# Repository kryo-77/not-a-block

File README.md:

# Not-a-block
Note block from Minecraft but in real life.

## What it is:
I made a note block from Minecraft which functions close enough to the actual game. You can tap the top face of the note block to play it and hit the back side of it to change the pitch (like right-clicking in Minecraft).

You can change the sound of the note block by placing it on different types of blocks as well. This is possible as there is an RFID card reader underneath the note block and a RFID tag on top of the instrument block (like stone, glass, sand, etc.)

## How it works:
The note block contains an ESP-32-C3-SuperMini. It's the microcontroller which connects to different components. It also stores music files inside its flash memory. 
As the music files are under a second, we can store quite a lot of them inside the ESP32, so there is no need for a SD card module (which also saves pins). Sound is played by a MAX98357A I2S amp with a 4Ω 3W speaker (50mm diameter).

There are 2 piezoelectric sensors present inside the note block's top and back surface. When you hit the surface, the piezo sends voltage to the ESP32's data pin which tells it to play the sound.

There are 16 different instrument sounds which the note block can play, which depend on the block below it. When the top surface is hit, it only tells ESP32 to play a single sound each time. When the back surface is hit, which is for changing the pitch of the instrument, each hit changes the sound to a different pitch. We don't need to have different audio inside the ESP32 for each pitch, as it can directly change on its own. Only the instrument sounds are needed to be stored.

For detecting which block is present below the note block, a PN532 RFID card reader sits on the bottom surface, while a RFID tag sits on the top surface of the other blocks. 
The tag gets read every few seconds so that if the block changes, its sound changes as well without a lot of delay. 4 magnets are also present under the note block's surface as well as an instrument block's top surface, so that lining up the tags as well as the blocks is very easy. The magnets are also in different polarities (NN/SS) on the surfaces so you don't accidentally misplace back of the note block (where you hit to change pitch).

The front surface of the note block contains holes so that the speaker can output sound. I decided to only make holes in the black layer as it is thinner than the white one and would not show that many holes as well. 

## Dimensions:
1) Note block / Instrument block: 10 x 10 x 10 cm
  - Each face has 3 layers, overall 0.4cm thick.
2) Note block PCB: 5.75 x 4 cm
3) Piezoelectric sensor: 3.5cm diameter

## Files:
- `CAD` folder contains .f3d (fusion) file & .stl for printing.
- `PCB` folder contains kicad files, `export.zip` has gerber files, `3d_model` has .step file of PCB. It has a `footprints_ext` folder which contains footprint for ESP32-C3-SuperMini which I downloaded online.
- `CODE` folder contains basic test code (when RFID card gets detected, a beep is produced) which uses a XIAO s3, MFRC522 RFID reader and no piezo sensor. I only had these components with me so code are based on it instead of the BOM.

## How to assemble / Details about the 3d printed parts (!!WIP!!)

There are two types of block: Note block and Instrument block. Note block contains the electronics while the instrument block only contains a single RFID tag + 4 magnets on its top surface.

There are 6 parts per block. Final assembly should measure 10x10x10cm.

The faces are different sizes as all need to fit together to form the 10x10x10cm. It is pretty easy to assemble as same dimension face are opposites of each other. 

Each face has a rectangular hole on its bottom surface and a rectangle sticking out on its top surface. 
The hole attaches to the `base plate`, while the rectangle goes in the `top plate`

Thats it for the assembly, just pushing the faces on to the base, no need for screws. Though the design might get changed depending on it actually works irl as I cant test the prints myself.

Screws aren't really needed other than mounting the pcb, that too is optional as I've made standoffs on the base plate. 

## PCB schematic / render

## BOM
| No | Component | Qty | Unit Price (USD) | Uses | Link |
|----|-----------|-----|------------------|------|------|
| 1 | ESP32-C3 SuperMini | 1 | 2.72 | MCU | https://makerbazar.in/products/esp32-c3-supermini-iot-development-board |
| 2 | PN532 RFID/NFC V3 module | 1 | 2.83 | RFID reader | https://robocraze.com/products/nfc-near-field-communication-rf-id-v3-module |
| 3 | MAX98357A I2S amplifier | 1 | 2.04 | Sound amplifier | https://robu.in/product/smartelex-i2s-audio-breakout-max98357a/ |
| 4 | Speaker, 4 ohm 3W | 1 | 1.05 | Sound output | Local shop |
| 5 | 35mm piezo sensor | 2 | 0.23 | Hit and pitch sensing | https://robocraze.com/products/35mm-piezo-sensor |
| 6 | BZX55C3V3 zener diode | 2 | 0.02 | Piezo protection | https://robu.in/product/bzx55c3v3-1-2w-zener-diode-pack-of-40/ |
| 7 | 4.7k resistor | 2 | n/a | Piezo protection | |
| 8 | 470uF polarised capacitor | 1 | n/a | Power smoothing | |
| 9 | 1N5819 Schottky diode | 1 | 0.06 | Power protection (USB and battery connected together) | https://robu.in/product/1n5819-ap-mcc-40v-1a-600mv1a-do-41-schottky-diodes-rohs/ |
| 10 |	3d print |	1 |	14.55 |	3d print | (printing legion channel - slack)	https://print.speedhawks.online/slice |
| 11 |	PCB |	1 |	9.48 |	PCB manufacturing	| https://robu.in/product/online-pcb-manufacturing-service/ |

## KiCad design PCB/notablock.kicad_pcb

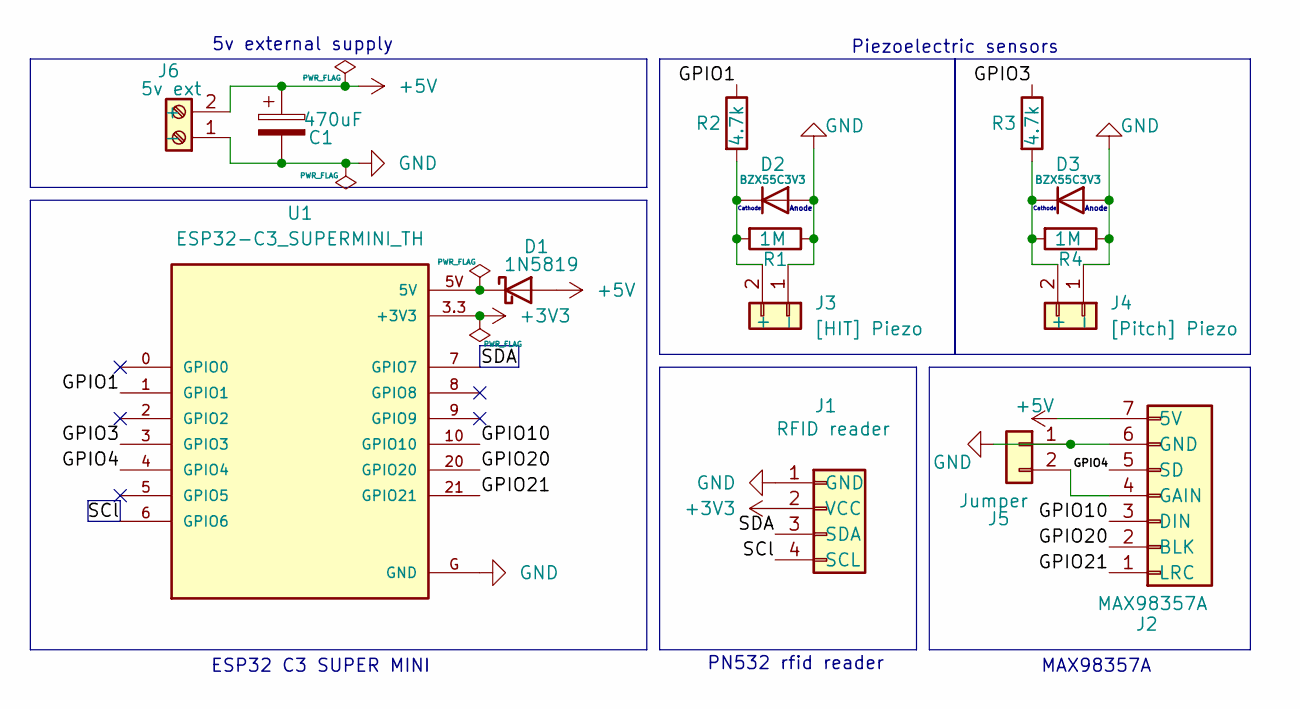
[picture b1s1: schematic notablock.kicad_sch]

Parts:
C1: 470uF; CP_Radial_D8.0mm_P3.50mm
D1: 1N5819; D_DO-41_SOD81_P2.54mm_Vertical_AnodeUp
D2, D3: BZX55C3V3; D_DO-41_SOD81_P2.54mm_Vertical_AnodeUp
J1: RFID reader; PinHeader_1x04_P2.54mm_Vertical
J2: MAX98357A; PinHeader_1x07_P2.54mm_Vertical
J3: [HIT] Piezo; PinHeader_1x02_P2.54mm_Vertical
J4: [Pitch] Piezo; PinHeader_1x02_P2.54mm_Vertical
J5: Jumper; PinHeader_1x02_P2.54mm_Vertical
J6: 5v ext; TerminalBlock_MaiXu_MX126-5.0-02P_1x02_P5.00mm
R1, R4: 1M; R_Axial_DIN0207_L6.3mm_D2.5mm_P2.54mm_Vertical
R2, R3: 4.7k; R_Axial_DIN0207_L6.3mm_D2.5mm_P2.54mm_Vertical
U1: ESP32-C3_SUPERMINI_TH; MODULE_ESP32-C3_SUPERMINI_TH

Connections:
+3V3: J1.2 (VCC), U1.3.3 (+3V3)
+5V: C1.1, D1.2 (A), J2.7 (5V), J6.2 (+)
/GPIO1: R2.1, U1.1 (GPIO1)
/GPIO3: R3.1, U1.3 (GPIO3)
/GPIO4: J2.5 (SD), U1.4 (GPIO4)
/GPIO10: J2.3 (DIN), U1.10 (GPIO10)
/GPIO20: J2.2 (BLK), U1.20 (GPIO20)
/GPIO21: J2.1 (LRC), U1.21 (GPIO21)
/SCl: J1.4 (SCL), U1.6 (GPIO6)
/SDA: J1.3 (SDA), U1.7 (GPIO7)
GND: C1.2, D2.2 (A), D3.2 (A), J1.1 (GND), J2.6 (GND), J3.1 (-), J4.1 (-), J5.1, J6.1 (-), R1.1, R4.1, U1.G (GND)
unnamed: D1.1 (K), U1.5V
unnamed: D2.1 (K), J3.2 (+), R1.2, R2.2
unnamed: D3.1 (K), J4.2 (+), R3.2, R4.2
unnamed: J2.4 (GAIN), J5.2

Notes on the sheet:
Anode
Piezoelectric sensors
Cathode
5v external supply
ESP32 C3 SUPER MINI
PN532 rfid reader
MAX98357A

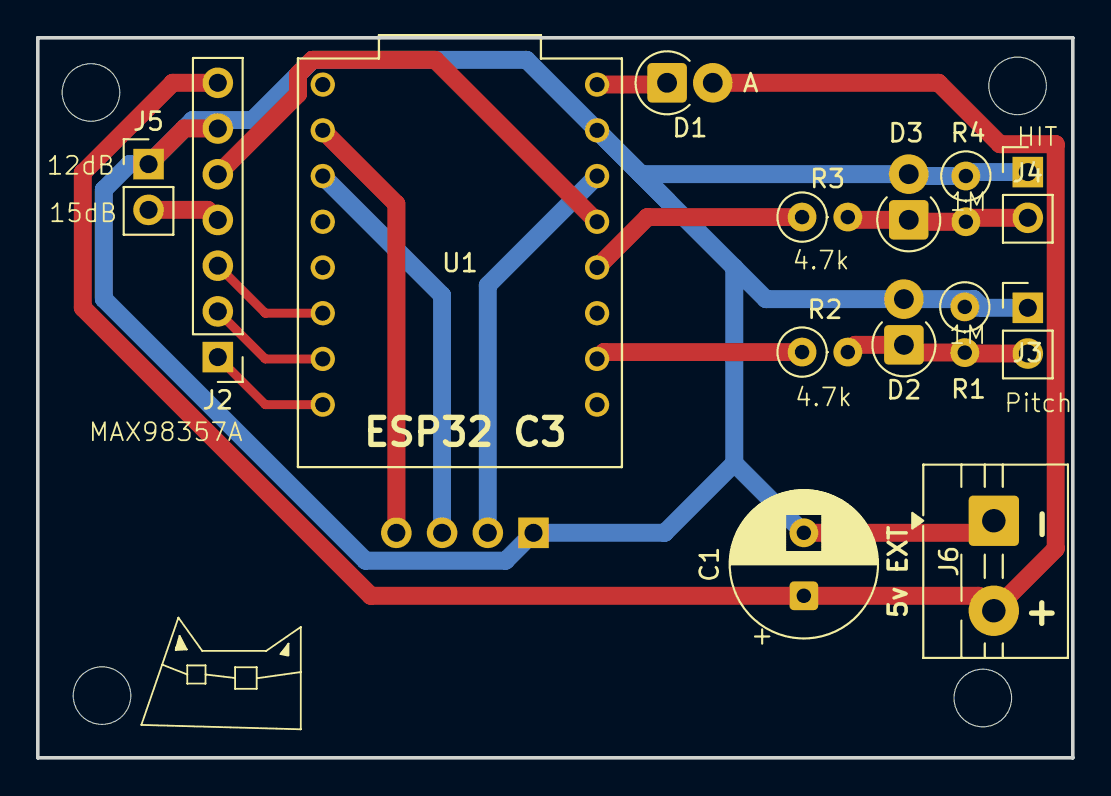
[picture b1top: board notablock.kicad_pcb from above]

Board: 2 copper layers, 57.5 x 40.0 mm, 15 parts (1 on the bottom side), 15 nets.

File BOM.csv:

No,Component,Qty,Unit Price (USD),Uses,Link
1,ESP32-C3 SuperMini,1,2.72,MCU,https://makerbazar.in/products/esp32-c3-supermini-iot-develo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
2,PN532 RFID/NFC V3 module,1,2.83,RFID reader,https://robocraze.com/products/nfc-near-field-communication-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
3,MAX98357A I2S amplifier,1,2.04,Sound amplifier,https://robu.in/product/smartelex-i2s-audio-breakout-max98357a/
4,"Speaker, 4 ohm 3W",1,1.05,Sound output,Local shop
5,35mm piezo sensor,2,0.23,Hit and pitch sensing,https://robocraze.com/products/35mm-piezo-sensor
6,BZX55C3V3 zener diode,2,0.02,Piezo protection,https://robu.in/product/bzx55c3v3-1-2w-zener-diode-pack-of-40/
7,4.7 resistor (unit TBD),2,n/a,Piezo protection,
8,470uF polarised capacitor,1,n/a,Power smoothing,
9,1N5819 Schottky diode,TBD,0.06,Power protection (USB and battery connected together),https://robu.in/product/1n5819-ap-mcc-40v-1a-600mv1a-do-41-s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
